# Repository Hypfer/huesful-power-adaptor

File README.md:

# HUEsful Power Adaptor

## Introduction

Sadly, the original power supply of Signify Philips Hue Playbars, Signe Table Lamps and more isn't particularly great.
They often have issues with a constant high-pitched whine and are overall very disappointing for the price tag.

You can't however simply replace it with a better 24V PSU, because Signify is using a gender-swapped borderline-proprietary connector for those.
Therefore, this project was born so that people have a better alternative than cutting open their power chords.

## Disclaimer

As always, you're using this at your own risk. It may void your warranty,
burn your house down or even leave hurtful comments on your latest social media posts.

You have been warned.

## Getting started

Check out the [releases section](https://github.com/Hypfer/huesful-power-adaptor/releases) for gerber files.

You can of course also download [KiCad](https://kicad-pcb.org/) (GPL V3) and plot those yourself.

## Specs

Signify is using a 6.5x3mm [CUI DEVICES PJ-048H DC Power Jack](https://www.cuidevices.com/product/resource/pj-048h.pdf) on their PSUs 
which is available via [DigiKey](https://www.digikey.de/product-detail/en/cui-devices/PJ-048H/CP-048H-ND/1644579) as well other suppliers.

There are three of those on this PCB. You don't have to populate all of them of course.

Furthermore, to connect a [proper PSU](https://www.amazon.de/-/en/LEICKE-Universal-Power-Supply-Plug/dp/B01GRYFNYK/), I've choosen the
[CUI DEVICES PJ-202BH DC Power Jack](https://www.cuidevices.com/product/resource/pj-202bh.pdf) which is a standard 5.5x2.5mm DC Power Jack
available via [DigiKey](https://www.digikey.com/en/products/detail/cui-devices/PJ-202BH/408451) as well as other suppliers.

You can also use a standard 5.08mm Terminal Block instead of one or more DC Power Jacks if you so desire.
That might be useful if you've already cut the power chord of your Hue Light in the past or want to daisy-chain multiple of these boards (not recommended).

## ToDo

A 3d printable case would be nice.

## License

This work is licensed under a
[Creative Commons Attribution-ShareAlike 4.0 International License][cc-by-sa].

[![CC BY-SA 4.0][cc-by-sa-image]][cc-by-sa]

[cc-by-sa]: http://creativecommons.org/licenses/by-sa/4.0/
[cc-by-sa-image]: ./img/cc-by-sa.png

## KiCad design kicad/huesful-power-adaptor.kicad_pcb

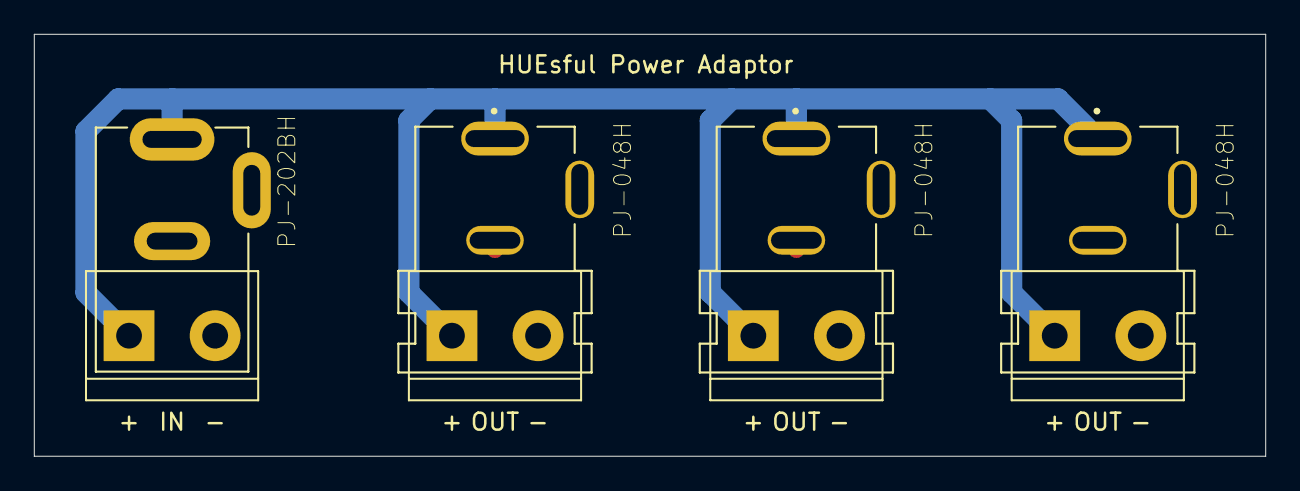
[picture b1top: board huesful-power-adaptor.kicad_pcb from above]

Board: 2 copper layers, 72.6 x 24.9 mm, 8 parts (0 on the bottom side), 2 nets.

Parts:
J5: IN; TerminalBlock_bornier-2_P5.08mm
J6: OUT 1; TerminalBlock_bornier-2_P5.08mm
J7: OUT 2; TerminalBlock_bornier-2_P5.08mm
J8: OUT 3; TerminalBlock_bornier-2_P5.08mm
PJ-048H, PJ-048H#2, PJ-048H#3: PJ-048H; CUI_PJ-048H
PJ-202BH: PJ-202BH; CUI_PJ-202BH

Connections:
GND: J5.2, J6.2, J7.2, J8.2, PJ-048H.2, PJ-048H#2.2, PJ-048H#3.2, PJ-202BH.2
unnamed: J5.1, J6.1, J7.1, J8.1, PJ-048H.1, PJ-048H#2.1, PJ-048H#3.1, PJ-202BH.1

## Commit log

2020-10-23 Initial Github Import

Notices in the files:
kicad/huesful-power-adaptor.kicad_pcb:
CC-BY-SA Hypfer
